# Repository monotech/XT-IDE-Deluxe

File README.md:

Monotech XT-IDE Deluxe v1.2 ReadMe
----

Bootable 8-bit ISA CF+IDE interface

Documentation for the switches can be found on the rear silkscreen.

If you wish to build one yourself, generate a gerber, and use the provided Bill Of Materials.
It uses a Keystone 9202 bracket, with a slot and hole cut for the CF slot and activity LED respectively.

I may have stock of these for sale at monotech.fwscart.com

Credit:
----
Design uses some of the schematic from XT-IDE Rev2 and Glitchworks
www.vcfed.org/forum/showthread.php?29202-XTIDE-Rev2
github.com/glitchwrks/xt_ide

The board is designed to carry XT-IDE Universal BIOS on the ROM
www.xtideuniversalbios.org

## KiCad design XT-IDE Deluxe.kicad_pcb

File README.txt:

Monotech XT-IDE rev 5.1 ReadMe
----------------------------

8-bit ISA IDE interface + Boot ROM (two separate functions that can be used individually).

Documentation for the switches can be found on the rear silkscreen.

Credit:
-------
Design uses schematic from Glitchworks, with a few small changes to switches
PCB is made from scratch with rough IC layout based on Glitchworks for ease of routing.
https://github.com/glitchwrks/xt_ide

XT-IDE Universal BIOS
https://code.google.com/archive/p/xtideuniversalbios/

Changelog:

rev 5.1:
Slightly different PCB shape so switches no longer protruded past PCB edge, getting in the way when pushing the card into a tight slot.
Some silkscreen documentation clarifying.
Changed capacitor hole spacing to much more common 5mm.

rev 5:
Initial release

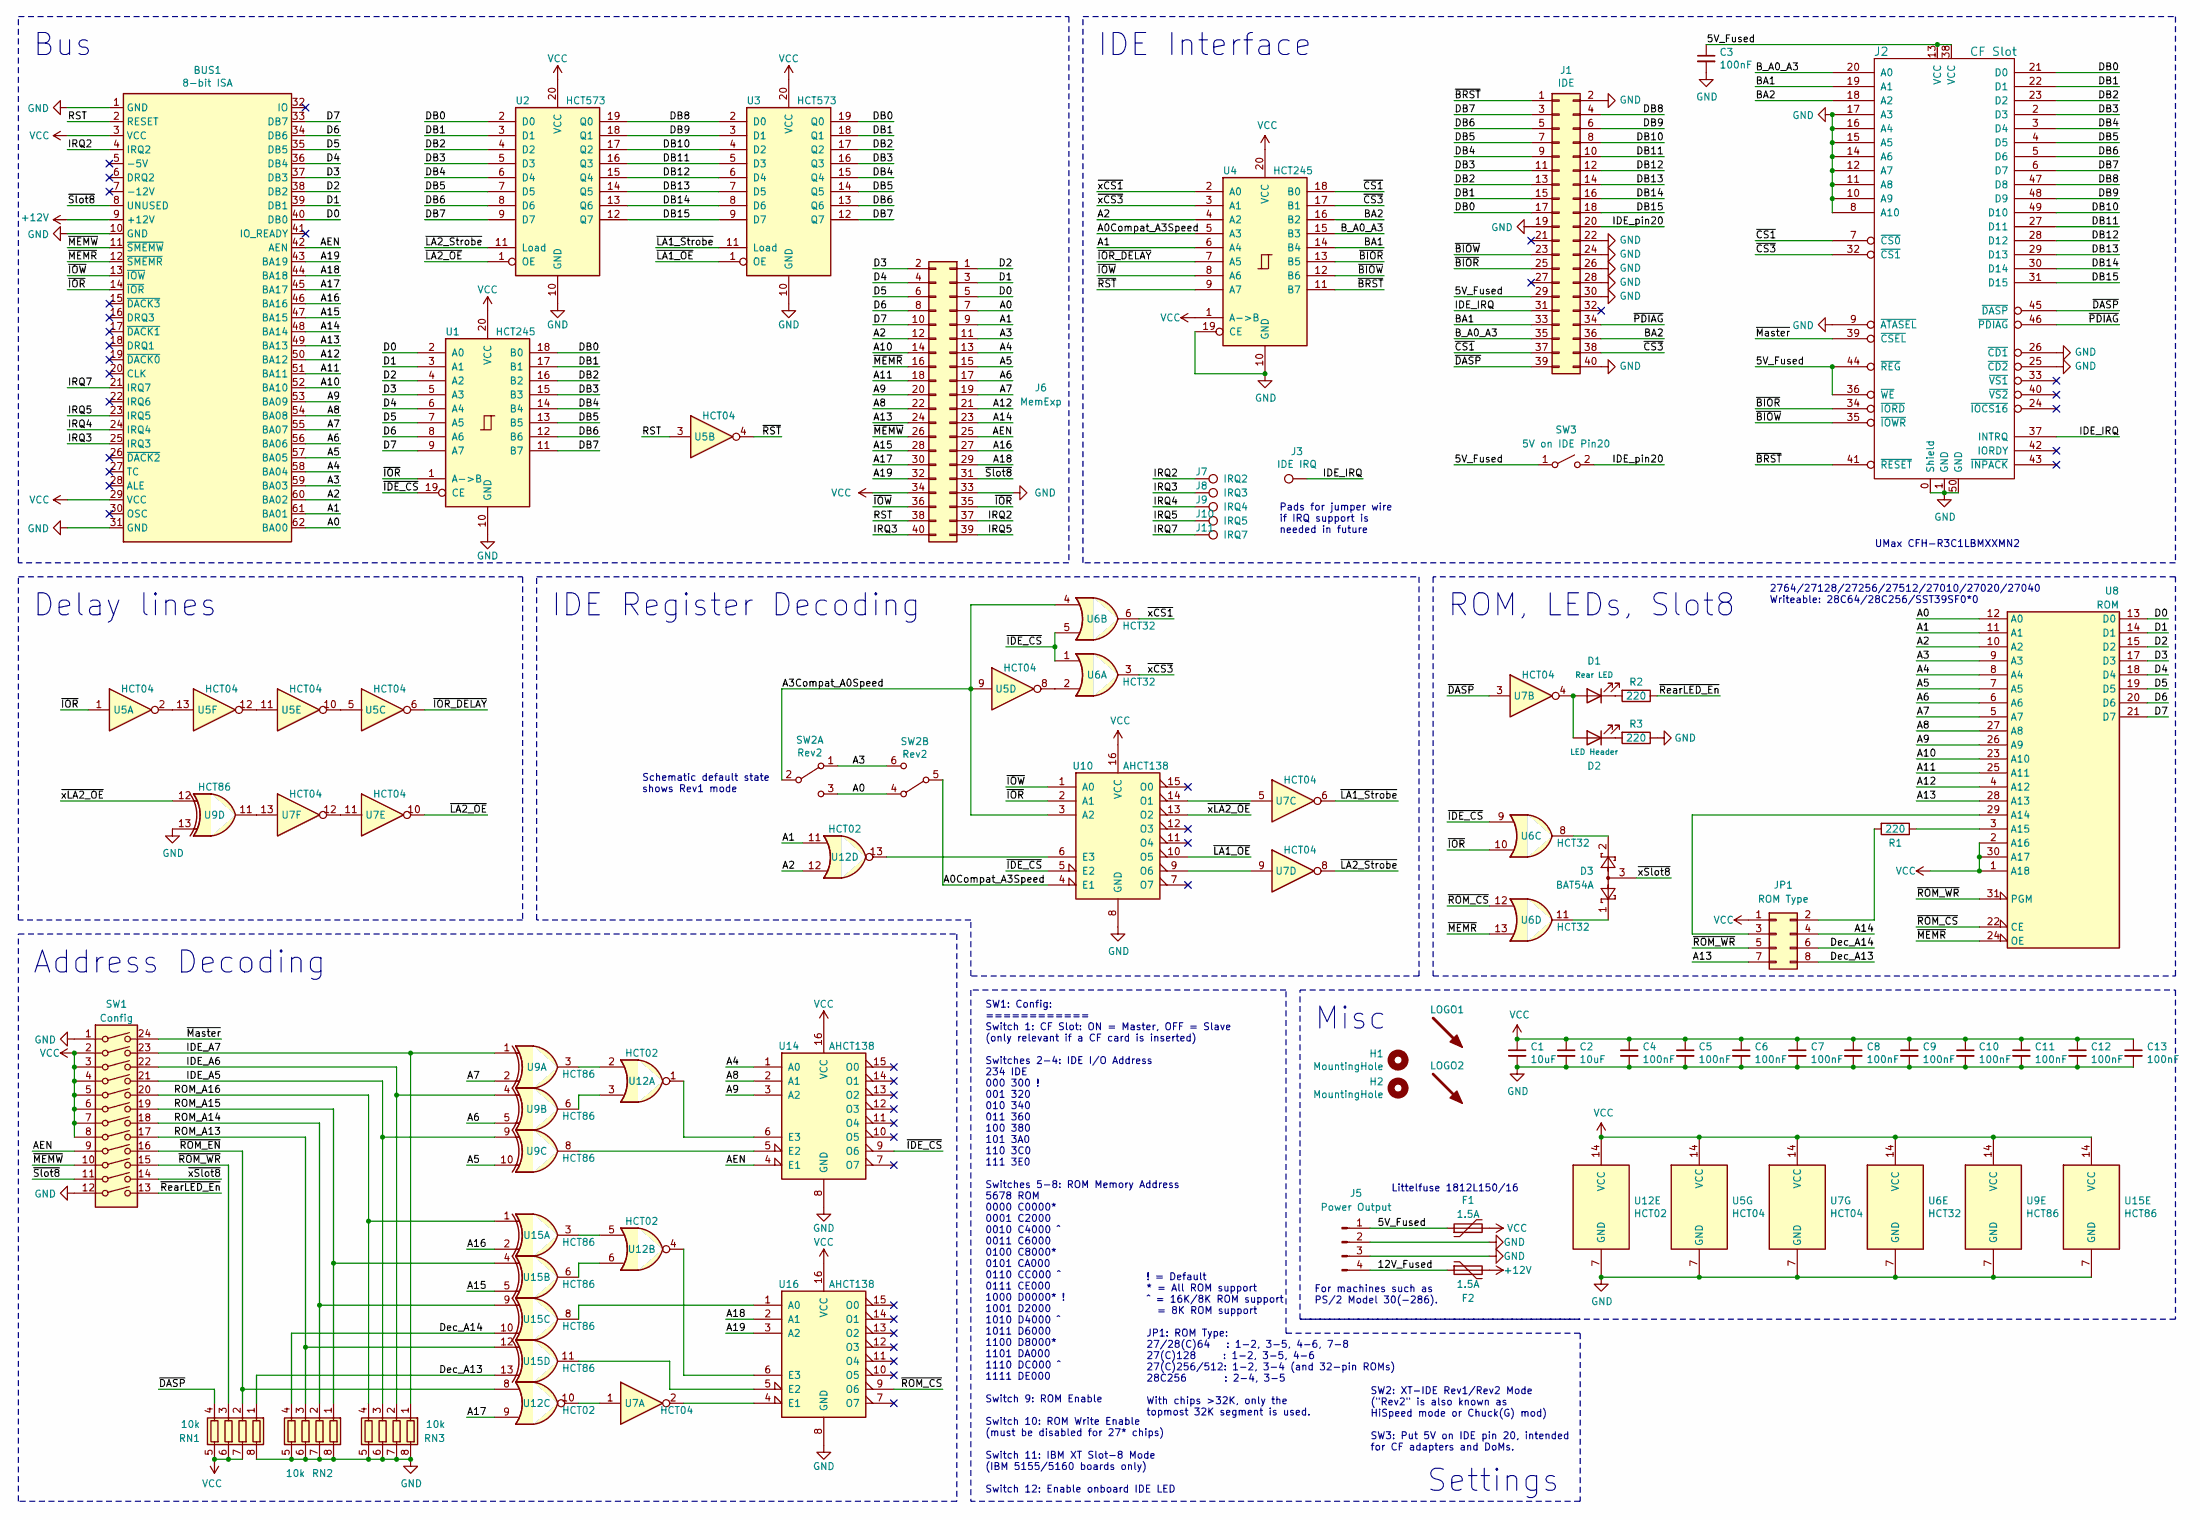
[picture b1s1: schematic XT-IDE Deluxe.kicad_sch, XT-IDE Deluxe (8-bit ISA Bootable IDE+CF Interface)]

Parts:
BUS1: 8-bit ISA; ISA-8BIT-XT-IDE
C1, C2: 10uF; C_0603_1608Metric
C3, C4, C5, C6, C7, C8, C9, C10, C11, C12, C13: 100nF; C_0603_1608Metric
D1: Rear LED; 3mm_LED_RightAngle
D2: LED Header; PinHeader_1x02_P2.54mm_Horizontal
D3: BAT54A; SOT-23
F1, F2: 1.5A; Fuse_1812_4532Metric
H1, H2: MountingHole; MountingHole_3.2mm_M3
J1: IDE; IDC-20_P2.54mm_Vertical_SMD
J2: CF Slot; CF_Slot_UMax_CFH-R3C1LBMXXMN2
J3: IDE IRQ; TestPoint_Pad_1.0x1.0mm
J5: Power Output; PinHeader_1x04_P2.54mm_Horizontal
J6: MemExp; MicroRAM_Expansion
J7: IRQ2; TestPoint_Pad_1.0x1.0mm
J8: IRQ3; TestPoint_Pad_1.0x1.0mm
J9: IRQ4; TestPoint_Pad_1.0x1.0mm
J10: IRQ5; TestPoint_Pad_1.0x1.0mm
J11: IRQ7; TestPoint_Pad_1.0x1.0mm
JP1: ROM Type; PinHeader_2x04_P2.54mm_Vertical_SMD
LOGO1: SYM_Arrow45_Large; Monotech Logo 12mm
LOGO2: SYM_Arrow45_Large; XT-IDE Deluxe
R1, R2, R3: 220; R_0805_2012Metric
RN1, RN2, RN3: 10k; R_Array_Convex_4x0603
SW1: Config; SW_DIP_SPSTx12_Slide_6.7x32.04mm_W8.61mm_P2.54mm_LowProfile
SW2: Rev2; SW_DPDT_MS-22D28-G020
SW3: 5V on IDE Pin20; SW_DPDT_MS-22D28-G020
U1, U4: HCT245; TSSOP-20_4.4x6.5mm_P0.65mm
U2, U3: HCT573; TSSOP-20_4.4x6.5mm_P0.65mm
U5, U7: HCT04; SOIC-14_3.9x8.7mm_P1.27mm
U6: HCT32; SOIC-14_3.9x8.7mm_P1.27mm
U8: ROM; DIP-32_W16.51mm_SMDSocket_LongPads
U9, U15: HCT86; SOIC-14_3.9x8.7mm_P1.27mm
U10, U14, U16: AHCT138; SOIC-16_3.9x9.9mm_P1.27mm
U12: HCT02; SOIC-14_3.9x8.7mm_P1.27mm

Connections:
+12V: BUS1.9 (+12V), F2.2
/5V_Fused: C3.1, F1.1, J1.29, J2.13 (VCC), J2.36 (~WE), J2.38 (VCC), J2.44 (~REG), J5.1, SW3.1 (A)
/12V_Fused: F2.1, J5.4
/A0: BUS1.62 (BA00), J6.7, SW2.3 (C), SW2.4 (A), U8.12 (A0)
/A0Compat_A3Speed: SW2.5 (B), U4.5 (A3), U10.4 (E1)
/A1: BUS1.61 (BA01), J6.9, U4.6 (A4), U8.11 (A1), U12.11
/A2: BUS1.60 (BA02), J6.12, U4.4 (A2), U8.10 (A2), U12.12
/A3: BUS1.59 (BA03), J6.11, SW2.1 (A), SW2.6 (C), U8.9 (A3)
/A3Compat_A0Speed: SW2.2 (B), U5.9, U6.4, U10.3 (A2)
/A4: BUS1.58 (BA04), J6.13, U8.8 (A4), U14.1 (A0)
/A5: BUS1.57 (BA05), J6.15, U8.7 (A5), U9.10
/A6: BUS1.56 (BA06), J6.17, U8.6 (A6), U9.5
/A7: BUS1.55 (BA07), J6.19, U8.5 (A7), U9.2
/A8: BUS1.54 (BA08), J6.22, U8.27 (A8), U14.2 (A1)
/A9: BUS1.53 (BA09), J6.20, U8.26 (A9), U14.3 (A2)
/A10: BUS1.52 (BA10), J6.14, U8.23 (A10)
/A11: BUS1.51 (BA11), J6.18, U8.25 (A11)
/A12: BUS1.50 (BA12), J6.21, U8.4 (A12)
/A13: BUS1.49 (BA13), J6.24, JP1.7, U8.28 (A13)
/A14: BUS1.48 (BA14), J6.23, JP1.4
/A15: BUS1.47 (BA15), J6.28, U15.5
/A16: BUS1.46 (BA16), J6.27, U15.2
/A17: BUS1.45 (BA17), J6.30, U12.9
/A18: BUS1.44 (BA18), J6.29, U16.2 (A1)
/A19: BUS1.43 (BA19), J6.32, U16.3 (A2)
/AEN: BUS1.42 (AEN), J6.25, SW1.9, U14.4 (E1)
/BA1: J1.33, J2.19 (A1), U4.14 (B4)
/BA2: J1.36, J2.18 (A2), U4.16 (B2)
/B_A0_A3: J1.35, J2.20 (A0), U4.15 (B3)
/D0: BUS1.40 (DB0), J6.5, U1.2 (A0), U8.13 (D0)
/D1: BUS1.39 (DB1), J6.3, U1.3 (A1), U8.14 (D1)
/D2: BUS1.38 (DB2), J6.1, U1.4 (A2), U8.15 (D2)
/D3: BUS1.37 (DB3), J6.2, U1.5 (A3), U8.17 (D3)
/D4: BUS1.36 (DB4), J6.4, U1.6 (A4), U8.18 (D4)
/D5: BUS1.35 (DB5), J6.6, U1.7 (A5), U8.19 (D5)
/D6: BUS1.34 (DB6), J6.8, U1.8 (A6), U8.20 (D6)
/D7: BUS1.33 (DB7), J6.10, U1.9 (A7), U8.21 (D7)
/DB0: J1.17, J2.21 (D0), U1.18 (B0), U2.2 (D0), U3.19 (Q0)
/DB1: J1.15, J2.22 (D1), U1.17 (B1), U2.3 (D1), U3.18 (Q1)
/DB2: J1.13, J2.23 (D2), U1.16 (B2), U2.4 (D2), U3.17 (Q2)
/DB3: J1.11, J2.2 (D3), U1.15 (B3), U2.5 (D3), U3.16 (Q3)
/DB4: J1.9, J2.3 (D4), U1.14 (B4), U2.6 (D4), U3.15 (Q4)
/DB5: J1.7, J2.4 (D5), U1.13 (B5), U2.7 (D5), U3.14 (Q5)
/DB6: J1.5, J2.5 (D6), U1.12 (B6), U2.8 (D6), U3.13 (Q6)
/DB7: J1.3, J2.6 (D7), U1.11 (B7), U2.9 (D7), U3.12 (Q7)
/DB8: J1.4, J2.47 (D8), U2.19 (Q0), U3.2 (D0)
/DB9: J1.6, J2.48 (D9), U2.18 (Q1), U3.3 (D1)
/DB10: J1.8, J2.49 (D10), U2.17 (Q2), U3.4 (D2)
/DB11: J1.10, J2.27 (D11), U2.16 (Q3), U3.5 (D3)
/DB12: J1.12, J2.28 (D12), U2.15 (Q4), U3.6 (D4)
/DB13: J1.14, J2.29 (D13), U2.14 (Q5), U3.7 (D5)
/DB14: J1.16, J2.30 (D14), U2.13 (Q6), U3.8 (D6)
/DB15: J1.18, J2.31 (D15), U2.12 (Q7), U3.9 (D7)
/Dec_A13: JP1.8, RN1.1 (R1.1), U15.13
/Dec_A14: JP1.6, RN2.4 (R4.1), U15.10
/IDE_A5: RN3.3 (R3.1), SW1.21, U9.9
/IDE_A6: RN3.2 (R2.1), SW1.22, U9.4
/IDE_A7: RN3.1 (R1.1), SW1.23, U9.1
/IDE_IRQ: J1.31, J2.37 (INTRQ), J3.1
/IDE_pin20: J1.20, SW3.2 (B)
/IRQ2: BUS1.4 (IRQ2), J6.37, J7.1
/IRQ3: BUS1.25 (IRQ3), J6.40, J8.1
/IRQ4: BUS1.24 (IRQ4), J9.1
/IRQ5: BUS1.23 (IRQ5), J6.39, J10.1
/IRQ7: BUS1.21 (IRQ7), J11.1
/ROM_A13: RN2.3 (R3.1), SW1.17, U15.12
/ROM_A14: RN2.2 (R2.1), SW1.18, U15.9
/ROM_A15: RN2.1 (R1.1), SW1.19, U15.4
/ROM_A16: RN3.4 (R4.1), SW1.20, U15.1
/RST: BUS1.2 (RESET), J6.38, U5.3
/~BIOR: J1.25, J2.34 (~IORD), U4.13 (B5)
/~BIOW: J1.23, J2.35 (~IOWR), U4.12 (B6)
/~BRST: J1.1, J2.41 (~RESET), U4.11 (B7)
/~CS1: J1.37, J2.7 (~CS0), U4.18 (B0)
/~CS3: J1.38, J2.32 (~CS1), U4.17 (B1)
/~DASP: J1.39, J2.45 (~DASP), RN1.4 (R4.1), U7.3
/~IDE_CS: U1.19 (CE), U6.1, U6.5, U6.9, U10.5 (E2), U14.9 (O6)
/~IOR_DELAY: U4.7 (A5), U5.6
/~IOR: BUS1.14 (~IOR), J6.35, U1.1 (A->B), U5.1, U6.10, U10.2 (A1)
/~IOW: BUS1.13 (~IOW), J6.36, U4.8 (A6), U10.1 (A0)
/~LA1_OE: U3.1 (OE), U10.10 (O5)
/~LA1_Strobe: U3.11 (Load), U7.6
/~LA2_OE: U2.1 (OE), U7.10
/~LA2_Strobe: U2.11 (Load), U7.8
/~MEMR: BUS1.12 (~SMEMR), J6.16, U6.13, U8.24 (OE)
/~MEMW: BUS1.11 (~SMEMW), J6.26, SW1.10
/~Master: J2.39 (~CSEL), SW1.24
/~PDIAG: J1.34, J2.46 (~PDIAG)
/~ROM_CS: U6.12, U8.22 (CE), U16.9 (O6)
/~ROM_EN: RN1.2 (R2.1), SW1.16, U12.8
/~ROM_WR: JP1.5, RN1.3 (R3.1), SW1.15, U8.31 (PGM)
/~RST: U4.9 (A7), U5.4
/~RearLED_En: R2.1, SW1.13
/~Slot8: BUS1.8 (UNUSED), J6.31, SW1.11
/~xCS1: U4.2 (A0), U6.6
/~xCS3: U4.3 (A1), U6.3
/~xLA2_OE: U9.12, U10.13 (O2)
/~xSlot8: D3.3, SW1.14
GND: BUS1.1 (GND), BUS1.10 (GND), BUS1.31 (GND), C1.2, C2.2, C3.2, C4.2, C5.2, C6.2, C7.2, C8.2, C9.2, C10.2, C11.2, C12.2, C13.2, J1.2, J1.19, J1.22, J1.24, J1.26, J1.28, J1.30, J1.40, J2.0 (Shield), J2.1 (GND), J2.8 (A10), J2.9 (~ATASEL), J2.10 (A9), J2.11 (A8), J2.12 (A7), J2.14 (A6), J2.15 (A5), J2.16 (A4), J2.17 (A3), J2.25 (~CD2), J2.26 (~CD1), J2.50 (GND), J5.2, J5.3, J6.33, R3.1, RN1.8 (R1.2), RN2.5 (R4.2), RN2.6 (R3.2), RN2.7 (R2.2), RN2.8 (R1.2), RN3.5 (R4.2), RN3.6 (R3.2), RN3.7 (R2.2), RN3.8 (R1.2), SW1.1, SW1.12, U1.10 (GND), U2.10 (GND), U3.10 (GND), U4.10 (GND), U4.19 (CE), U5.7 (GND), U6.7 (GND), U7.7 (GND), U8.16 (GND), U9.7 (GND), U9.13, U10.8 (GND), U12.7 (GND), U14.8 (GND), U15.7 (GND), U16.8 (GND)
unnamed: D1.1 (K), R2.2
unnamed: D1.2 (A), D2.2 (A), U7.4
unnamed: D2.1 (K), R3.2
unnamed: D3.1, U6.11
unnamed: D3.2, U6.8
unnamed: JP1.2, R1.2
unnamed: JP1.3, U8.29 (A14)
unnamed: R1.1, U8.3 (A15)
unnamed: U5.8, U6.2
unnamed: U5.5, U5.10
unnamed: U5.11, U5.12
unnamed: U5.2, U5.13
unnamed: U7.11, U7.12
unnamed: U7.13, U9.11
unnamed: U10.6 (E3), U12.13
unnamed: U7.9, U10.9 (O6)
unnamed: U7.5, U10.14 (O1)
unnamed: U12.1, U14.6 (E3)
unnamed: U9.3, U12.2
unnamed: U9.6, U12.3
unnamed: U12.4, U16.6 (E3)
unnamed: U12.5, U15.3
unnamed: U12.6, U15.6
unnamed: U7.1, U12.10
unnamed: U9.8, U14.5 (E2)
unnamed: U15.8, U16.1 (A0)
unnamed: U15.11, U16.5 (E2)
unnamed: U7.2, U16.4 (E1)
VCC: BUS1.3 (VCC), BUS1.29 (VCC), C1.1, C2.1, C4.1, C5.1, C6.1, C7.1, C8.1, C9.1, C10.1, C11.1, C12.1, C13.1, F1.2, J6.34, JP1.1, RN1.5 (R4.2), RN1.6 (R3.2), RN1.7 (R2.2), SW1.2, SW1.3, SW1.4, SW1.5, SW1.6, SW1.7, SW1.8, U1.20 (VCC), U2.20 (VCC), U3.20 (VCC), U4.1 (A->B), U4.20 (VCC), U5.14 (VCC), U6.14 (VCC), U7.14 (VCC), U8.1 (A18), U8.2 (A16), U8.30 (A17), U8.32 (VCC), U9.14 (VCC), U10.16 (VCC), U12.14 (VCC), U14.16 (VCC), U15.14 (VCC), U16.16 (VCC)

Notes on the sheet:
Bus
Littelfuse 1812L150/16
For machines such as PS/2 Model 30(-286).
! = Default * = All ROM support ^ = 16K/8K ROM support = 8K ROM support JP1: ROM Type: 27/28(C)64 : 1-2, 3-5, 4-6, 7-8 27(C)128 : 1-2, 3-5, 4-6 27(C)256/512: 1-2, 3-4 (and 32-pin ROMs) 28C256 : 2-4, 3-5 With chips >32K, only the topmost 32K segment is used.
Misc
IDE Register Decoding
Pads for jumper wire if IRQ support is needed in future
SW2: XT-IDE Rev1/Rev2 Mode ("Rev2" is also known as HiSpeed mode or Chuck(G) mod) SW3: Put 5V on IDE pin 20, intended for CF adapters and DoMs.
Delay lines
IDE Interface
SW1: Config: ============ Switch 1: CF Slot: ON = Master, OFF = Slave (only relevant if a CF card is inserted) Switches 2-4: IDE I/O Address 234 IDE 000 300 ! 001 320 010 340 011 360 100 380 101 3A0 110 3C0 111 3E0 Switches 5-8: ROM Memory Address 5678 ROM 0000 C0000* 0001 C2000 0010 C4000 ^ 0011 C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
Schematic default state shows Rev1 mode
UMax CFH-R3C1LBMXXMN2
2764/27128/27256/27512/27010/27020/27040 Writeable: 28C64/28C256/SST39SF0*0
ROM, LEDs, Slot8
Address Decoding
Settings

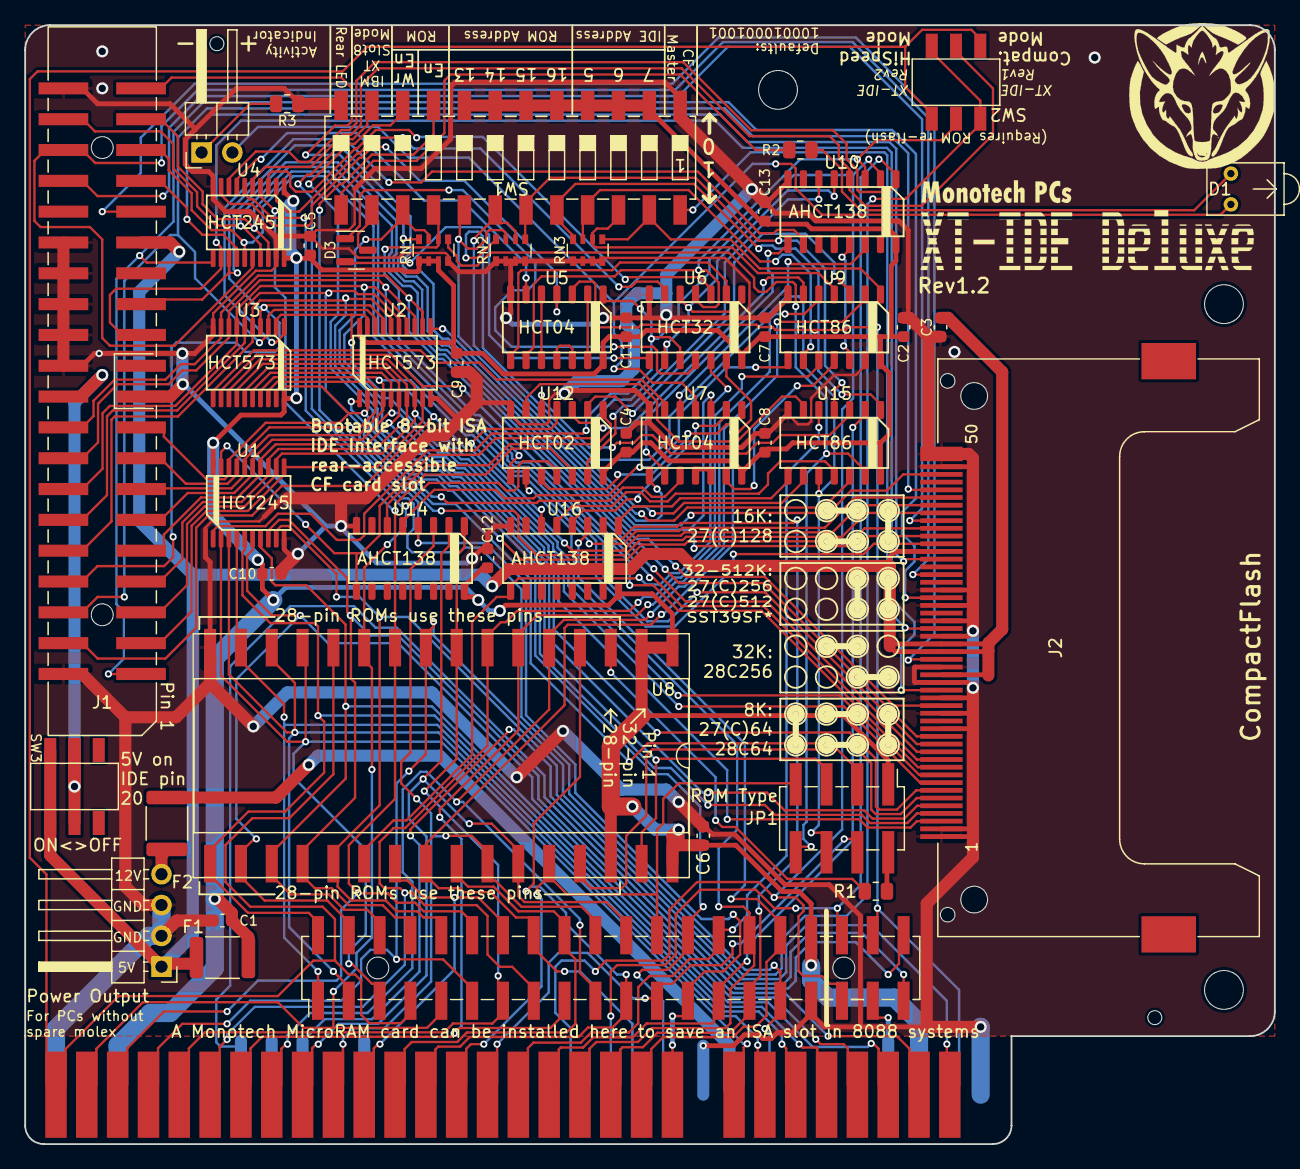
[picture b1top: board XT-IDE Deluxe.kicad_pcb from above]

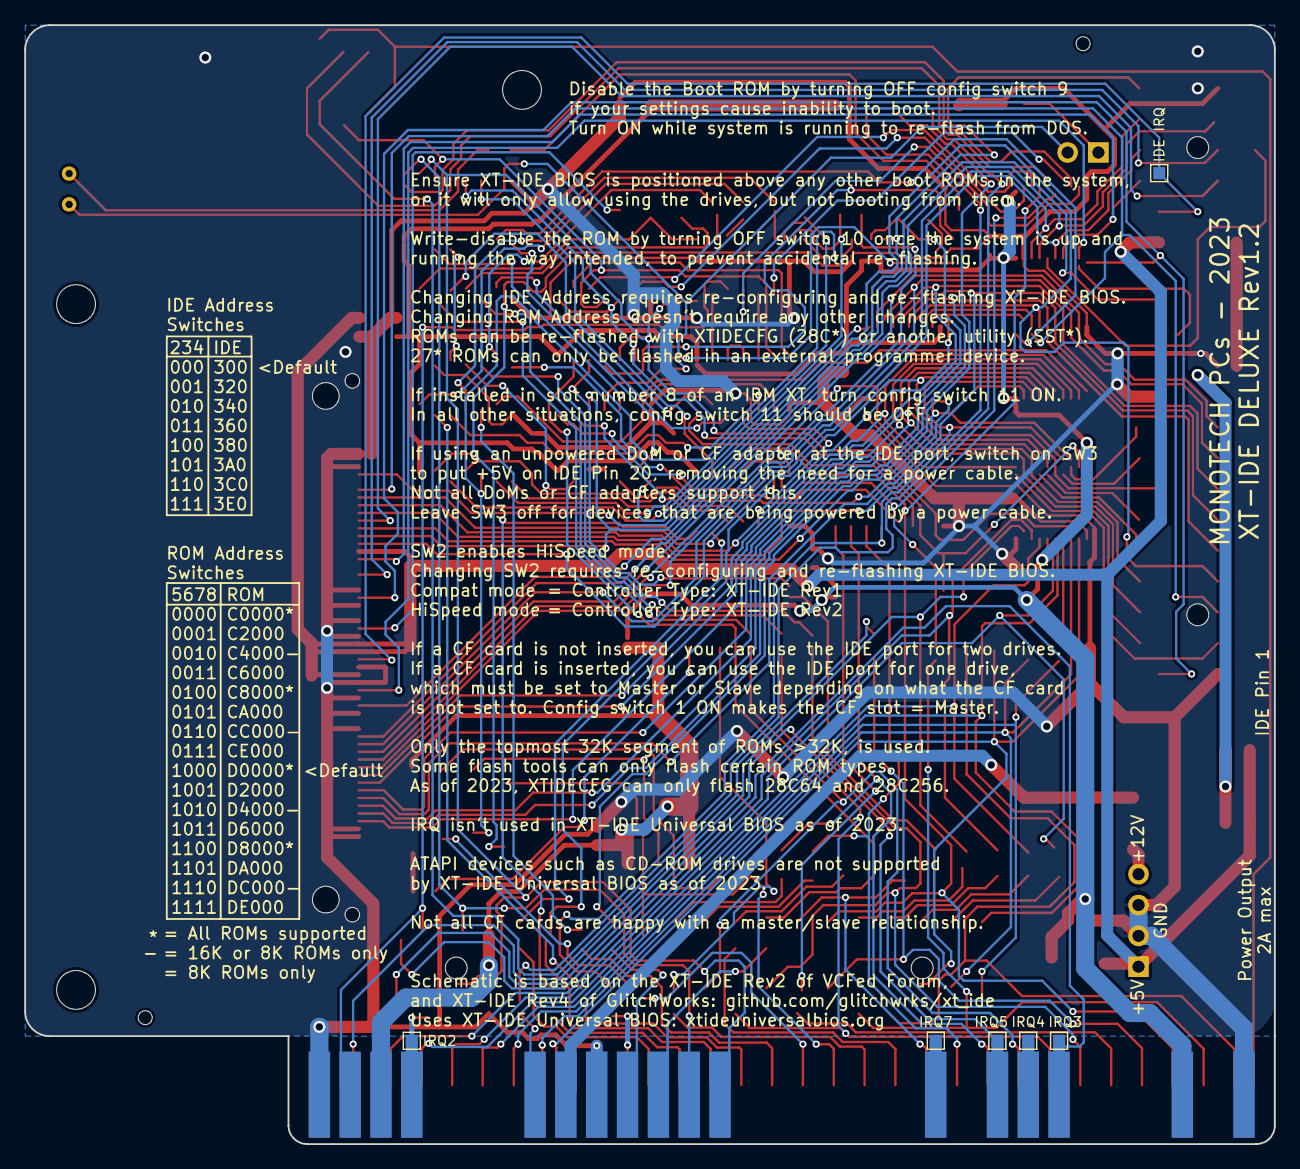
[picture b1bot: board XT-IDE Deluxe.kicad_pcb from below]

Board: 2 copper layers, 103.0 x 92.2 mm, 57 parts (6 on the bottom side), 128 nets.

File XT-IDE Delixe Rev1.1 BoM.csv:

Ref,Qnty,Value,Footprint,Mouser Part
"C1, C2, ",2,10uF,0805,187-CL21A106KOQNNNG 
"C3, C4, C5, C6, C7, C8, C9, C10, C11, C12, ",10,100nF,0805,603-CC805KRX7R9BB104 
"D1, ",1,LED,0805,710-150080SS75000 
"D2, ",1,LED,2.54mm,649-1012937990202BLF 
"F1, F2, ",2,1.5A,1206,530-C1T1.5 
"J1, ",1,IDE,IDC-40,710-61204021621 
"J2, ",1,CF_Adapter,2x20_2.54mm,710-61304021821 
"J5, ",1,Power Output,,571-1718264 
"J6, ",1,MemExp,2x17_2.54mm,649-67996-434HLF 
"JP1, ",1,5V on IDE Pin20,2.54mm,649-54102-T0800LF 
"R1, R2, ",2,1k,0805,652-CRT0805FZ1001ELF 
"RN1, RN2, RN3, ",3,10k,4x0603,791-WA06X103JTL 
"SW1, ",1,HiSpeed,,611-JS202011CQN 
"SW2, ",1,Config,DIP-24,774-20812 
"U1, U4, ",2,HCT245,TSSOP-20,595-SN74HCT245PW 
"U2, U3, ",2,HCT573,SOIC-20,863-MC74HCT573ADWG 
"U5, U7, ",2,HCT04,SOIC-14,595-SN74HCT04DRG4 
"U6, ",1,HCT32,SOIC-14,595-SN74HCT32D 
"U8, ",1,DIP_Socket,DIP-28,571-1-2199299-2 
"U9, U15, ",2,HCT86,SOIC-14,595-CD74HCT86M 
"U10, U14, U16, ",3,F138,SOIC-16,595-SN74F138D 
"U12, ",1,HCT02,SOIC-14,595-SN74HCT02DR 
"U13, ",1,AHC1G09,SC-70-5,595-SN74AHC1G09DCKR

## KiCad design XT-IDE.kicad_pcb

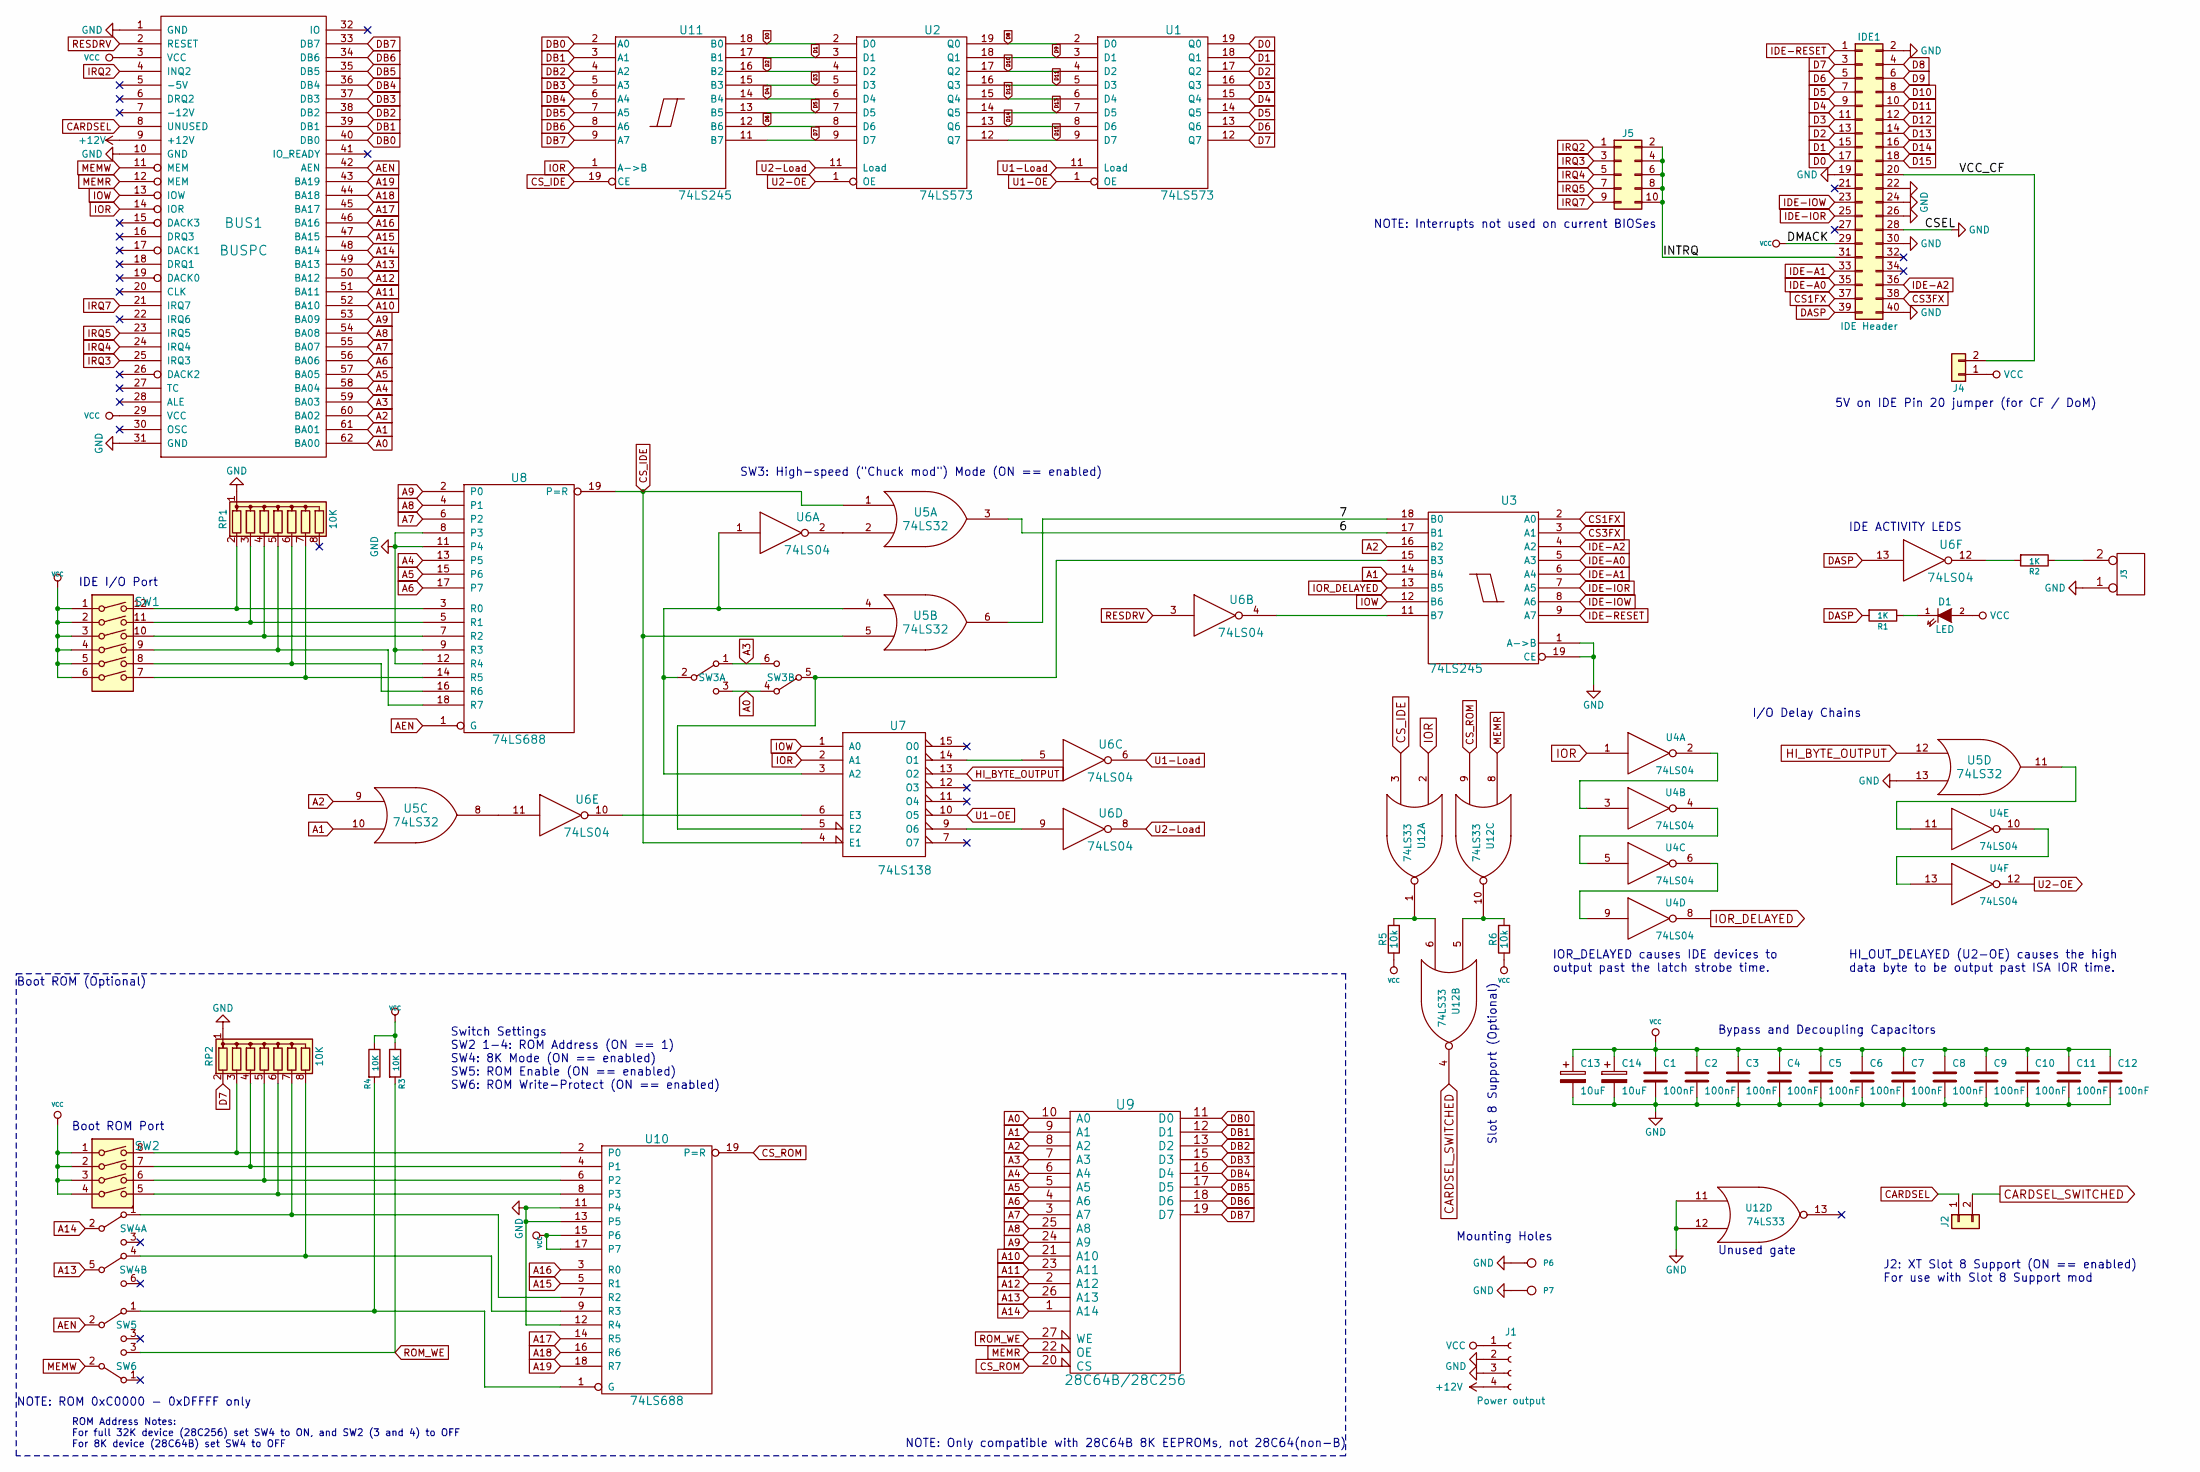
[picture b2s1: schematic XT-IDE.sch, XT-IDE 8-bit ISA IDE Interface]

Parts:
BUS1: BUSPC; ISA-8BIT-XT-IDE
C1, C2, C3, C4, C5, C6, C7, C8, C9, C10, C11: 100nF; C_Disc_D4.3mm_W1.9mm_P5.00mm
C12: 100nF; C_0805_2012Metric_Pad1.15x1.40mm_HandSolder
C13, C14: 10uF; CP_Radial_Tantal_D4.5mm_P5.00mm
D1: LED; LED_D5.0mm
IDE1: IDE Header; Pin_Header_Angled_2x20_Pitch2.54mm_Shrouded
J1: Power output; PinHeader_1x04_P2.54mm_Horizontal
J2, J4: Conn_01x02; PinHeader_1x02_P2.54mm_Vertical
J3: External LED; PinHeader_1x02_P2.54mm_Horizontal
J5: Conn_02x05_Odd_Even; PinHeader_2x05_P2.54mm_Vertical
P6, P7: CONN_1; MountingHole_3.2mm_M3
R1, R2: 1K; R_Axial_DIN0207_L6.3mm_D2.5mm_P7.62mm_Horizontal
R3, R4: 10K; R_Axial_DIN0207_L6.3mm_D2.5mm_P7.62mm_Horizontal
R5, R6: 10k; R_0805_2012Metric_Pad1.15x1.40mm_HandSolder
RP1, RP2: 10K; R_Array_SIP9
SW1: IDE Address; SW_DIP_SPSTx06_Slide_9.78x17.42mm_W7.62mm_P2.54mm
SW2: ROM Address; SW_DIP_SPSTx04_Slide_9.78x12.34mm_W7.62mm_P2.54mm
SW3: DPDT; CKCOMP-OS202011MA0QS1
SW4: DPDT; SW_MS-22D18G2
SW5, SW6: SPDT; SW_CuK_OS102011MA1QN1_SPDT_Angled
U1, U2: 74LS573; DIP-20_W7.62mm
U3, U11: 74LS245; DIP-20_W7.62mm
U4, U6: 74LS04; DIP-14_W7.62mm
U5: 74LS32; DIP-14_W7.62mm
U7: 74LS138; DIP-16_W7.62mm
U8, U10: 74LS688; DIP-20_W7.62mm
U9: 28C64B/28C256; DIP-28_W15.24mm_Socket
U12: 74LS33; SOIC-14_3.9x8.7mm_P1.27mm

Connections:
+12V: BUS1.9 (+12V), J1.4
/6: U3.17 (B1), U5.3
/7: U3.18 (B0), U5.6
/INTRQ: IDE1.31, J5.2, J5.4, J5.6, J5.8, J5.10
/VCC_CF: IDE1.20, J4.2
A0: BUS1.62 (BA00), SW3.3 (C), SW3.4 (A), U9.10 (A0)
A1: BUS1.61 (BA01), U3.14 (B4), U5.10, U9.9 (A1)
A2: BUS1.60 (BA02), U3.16 (B2), U5.9, U9.8 (A2)
A3: BUS1.59 (BA03), SW3.1 (A), SW3.6 (C), U9.7 (A3)
A4: BUS1.58 (BA04), U8.13 (P5), U9.6 (A4)
A5: BUS1.57 (BA05), U8.15 (P6), U9.5 (A5)
A6: BUS1.56 (BA06), U8.17 (P7), U9.4 (A6)
A7: BUS1.55 (BA07), U8.6 (P2), U9.3 (A7)
A8: BUS1.54 (BA08), U8.4 (P1), U9.25 (A8)
A9: BUS1.53 (BA09), U8.2 (P0), U9.24 (A9)
A10: BUS1.52 (BA10), U9.21 (A10)
A11: BUS1.51 (BA11), U9.23 (A11)
A12: BUS1.50 (BA12), U9.2 (A12)
A13: BUS1.49 (BA13), SW4.5 (B), U9.26 (A13)
A14: BUS1.48 (BA14), SW4.2 (B), U9.1 (A14)
A15: BUS1.47 (BA15), U10.5 (R1)
A16: BUS1.46 (BA16), U10.3 (R0)
A17: BUS1.45 (BA17), U10.14 (R5)
A18: BUS1.44 (BA18), U10.16 (R6)
A19: BUS1.43 (BA19), U10.18 (R7)
AEN: BUS1.42 (AEN), SW5.2 (B), U8.1 (G)
CARDSEL: BUS1.8 (UNUSED), J2.1
CARDSEL_SWITCHED: J2.2, U12.4
CS1FX: IDE1.37, U3.2 (A0)
CS3FX: IDE1.38, U3.3 (A1)
CS_IDE: U5.1, U5.5, U7.4 (E1), U8.19 (P=R), U11.19 (CE), U12.3
CS_ROM: U9.20 (CS), U10.19 (P=R), U12.9
D0: IDE1.17, U1.19 (Q0), U2.2 (D0), U11.18 (B0)
D1: IDE1.15, U1.18 (Q1), U2.3 (D1), U11.17 (B1)
D2: IDE1.13, U1.17 (Q2), U2.4 (D2), U11.16 (B2)
D3: IDE1.11, U1.16 (Q3), U2.5 (D3), U11.15 (B3)
D4: IDE1.9, U1.15 (Q4), U2.6 (D4), U11.14 (B4)
D5: IDE1.7, U1.14 (Q5), U2.7 (D5), U11.13 (B5)
D6: IDE1.5, U1.13 (Q6), U2.8 (D6), U11.12 (B6)
D7: IDE1.3, RP2.2 (R1), U1.12 (Q7), U2.9 (D7), U11.11 (B7)
D8: IDE1.4, U1.2 (D0), U2.19 (Q0)
D9: IDE1.6, U1.3 (D1), U2.18 (Q1)
D10: IDE1.8, U1.4 (D2), U2.17 (Q2)
D11: IDE1.10, U1.5 (D3), U2.16 (Q3)
D12: IDE1.12, U1.6 (D4), U2.15 (Q4)
D13: IDE1.14, U1.7 (D5), U2.14 (Q5)
D14: IDE1.16, U1.8 (D6), U2.13 (Q6)
D15: IDE1.18, U1.9 (D7), U2.12 (Q7)
DASP: IDE1.39, R1.2, U6.13
DB0: BUS1.40 (DB0), U9.11 (D0), U11.2 (A0)
DB1: BUS1.39 (DB1), U9.12 (D1), U11.3 (A1)
DB2: BUS1.38 (DB2), U9.13 (D2), U11.4 (A2)
DB3: BUS1.37 (DB3), U9.15 (D3), U11.5 (A3)
DB4: BUS1.36 (DB4), U9.16 (D4), U11.6 (A4)
DB5: BUS1.35 (DB5), U9.17 (D5), U11.7 (A5)
DB6: BUS1.34 (DB6), U9.18 (D6), U11.8 (A6)
DB7: BUS1.33 (DB7), U9.19 (D7), U11.9 (A7)
GND: BUS1.1 (GND), BUS1.10 (GND), BUS1.31 (GND), C1.2, C2.2, C3.2, C4.2, C5.2, C6.2, C7.2, C8.2, C9.2, C10.2, C11.2, C12.2, C13.2, C14.2, IDE1.2, IDE1.19, IDE1.22, IDE1.24, IDE1.26, IDE1.28, IDE1.30, IDE1.40, J1.2, J1.3, J3.1, P6.1, P7.1, RP1.1 (common), RP2.1 (common), U1.10 (GND), U2.10 (GND), U3.1 (A->B), U3.10 (GND), U3.19 (CE), U4.7 (GND), U5.7 (GND), U5.13, U6.7 (GND), U7.8 (GND), U8.8 (P3), U8.9 (R3), U8.10 (GND), U8.11 (P4), U8.12 (R4), U9.14 (GND), U10.10 (GND), U10.11 (P4), U10.12 (R4), U10.13 (P5), U11.10 (GND), U12.7 (GND), U12.11, U12.12
HI_BYTE_OUTPUT: U5.12, U7.13 (O2)
IDE-A0: IDE1.35, U3.5 (A3)
IDE-A1: IDE1.33, U3.6 (A4)
IDE-A2: IDE1.36, U3.4 (A2)
IDE-IOR: IDE1.25, U3.7 (A5)
IDE-IOW: IDE1.23, U3.8 (A6)
IDE-RESET: IDE1.1, U3.9 (A7)
IOR: BUS1.14 (IOR), U4.1, U7.2 (A1), U11.1 (A->B), U12.2
IOR_DELAYED: U3.13 (B5), U4.8
IOW: BUS1.13 (IOW), U3.12 (B6), U7.1 (A0)
IRQ2: BUS1.4 (INQ2), J5.1
IRQ3: BUS1.25 (IRQ3), J5.3
IRQ4: BUS1.24 (IRQ4), J5.5
IRQ5: BUS1.23 (IRQ5), J5.7
IRQ7: BUS1.21 (IRQ7), J5.9
MEMR: BUS1.12 (MEM), U9.22 (OE), U12.8
MEMW: BUS1.11 (MEM), SW6.2 (B)
unnamed: D1.1 (K), R1.1
unnamed: J3.2 (PM), R2.1
unnamed: R2.2, U6.12
unnamed: R4.2, SW5.1 (A), U10.1 (G)
unnamed: R5.2, U12.1, U12.6
unnamed: R6.2, U12.5, U12.10
unnamed: RP1.2 (R1), SW1.12, U8.3 (R0)
unnamed: RP1.3 (R2), SW1.11, U8.5 (R1)
unnamed: RP1.4 (R3), SW1.10, U8.7 (R2)
unnamed: RP1.5 (R4), SW1.9, U8.18 (R7)
unnamed: RP1.6 (R5), SW1.8, U8.16 (R6)
unnamed: RP1.7 (R6), SW1.7, U8.14 (R5)
unnamed: RP2.3 (R2), SW2.8, U10.2 (P0)
unnamed: RP2.4 (R3), SW2.7, U10.4 (P1)
unnamed: RP2.5 (R4), SW2.6, U10.6 (P2)
unnamed: RP2.6 (R5), SW2.5, U10.8 (P3)
unnamed: RP2.7 (R6), SW4.1 (A), U10.7 (R2)
unnamed: RP2.8 (R7), SW4.4 (A), U10.9 (R3)
unnamed: SW3.2 (B), U5.4, U6.1, U7.3 (A2)
unnamed: SW3.5 (B), U3.15 (B3), U7.5 (E2)
unnamed: U3.11 (B7), U6.4
unnamed: U4.2, U4.3
unnamed: U4.4, U4.5
unnamed: U4.6, U4.9
unnamed: U4.10, U4.13
unnamed: U4.11, U5.11
unnamed: U5.2, U6.2
unnamed: U5.8, U6.11
unnamed: U6.5, U7.14 (O1)
unnamed: U6.9, U7.9 (O6)
unnamed: U6.10, U7.6 (E3)
RESDRV: BUS1.2 (RESET), U6.3
ROM_WE: R3.2, SW6.3 (C), U9.27 (WE)
U1-Load: U1.11 (Load), U6.6
U1-OE: U1.1 (OE), U7.10 (O5)
U2-Load: U2.11 (Load), U6.8
U2-OE: U2.1 (OE), U4.12
VCC: BUS1.3 (VCC), BUS1.29 (VCC), C1.1, C2.1, C3.1, C4.1, C5.1, C6.1, C7.1, C8.1, C9.1, C10.1, C11.1, C12.1, C13.1, C14.1, D1.2 (A), IDE1.29, J1.1, J4.1, R3.1, R4.1, R5.1, R6.1, SW1.1, SW1.2, SW1.3, SW1.4, SW1.5, SW1.6, SW2.1, SW2.2, SW2.3, SW2.4, U1.20 (VCC), U2.20 (VCC), U3.20 (VCC), U4.14 (VCC), U5.14 (VCC), U6.14 (VCC), U7.16 (VCC), U8.20 (VCC), U9.28 (VCC), U10.15 (P6), U10.17 (P7), U10.20 (VCC), U11.20 (VCC), U12.14 (VCC)

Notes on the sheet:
5V on IDE Pin 20 jumper (for CF / DoM)
IDE ACTIVITY LEDS
IDE I/O Port
SW3: High-speed ("Chuck mod") Mode (ON == enabled)
NOTE: Only compatible with 28C64B 8K EEPROMs, not 28C64(non-B)
NOTE: ROM 0xC0000 - 0xDFFFF only
Switch Settings SW2 1-4: ROM Address (ON == 1) SW4: 8K Mode (ON == enabled) SW5: ROM Enable (ON == enabled) SW6: ROM Write-Protect (ON == enabled)
ROM Address Notes: For full 32K device (28C256) set SW4 to ON, and SW2 (3 and 4) to OFF For 8K device (28C64B) set SW4 to OFF
Boot ROM (Optional)
Mounting Holes
Bypass and Decoupling Capacitors
NOTE: Interrupts not used on current BIOSes
J2: XT Slot 8 Support (ON == enabled) For use with Slot 8 Support mod
I/O Delay Chains
IOR_DELAYED causes IDE devices to output past the latch strobe time.
HI_OUT_DELAYED (U2-OE) causes the high data byte to be output past ISA IOR time.
Slot 8 Support (Optional)
Boot ROM Port
Unused gate

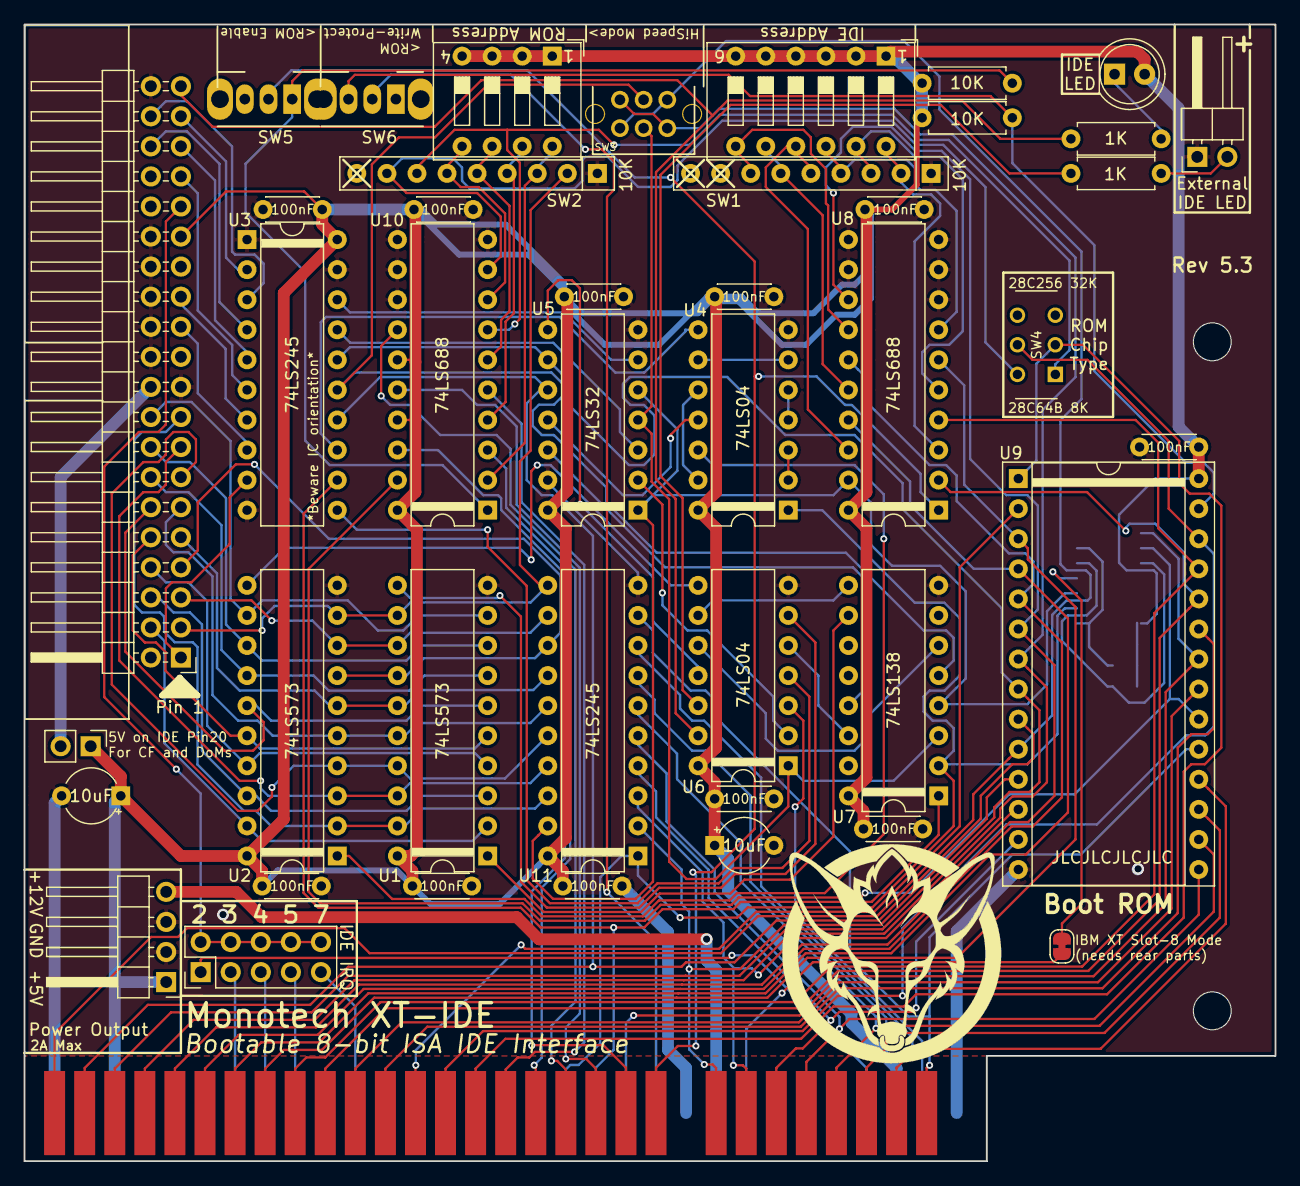
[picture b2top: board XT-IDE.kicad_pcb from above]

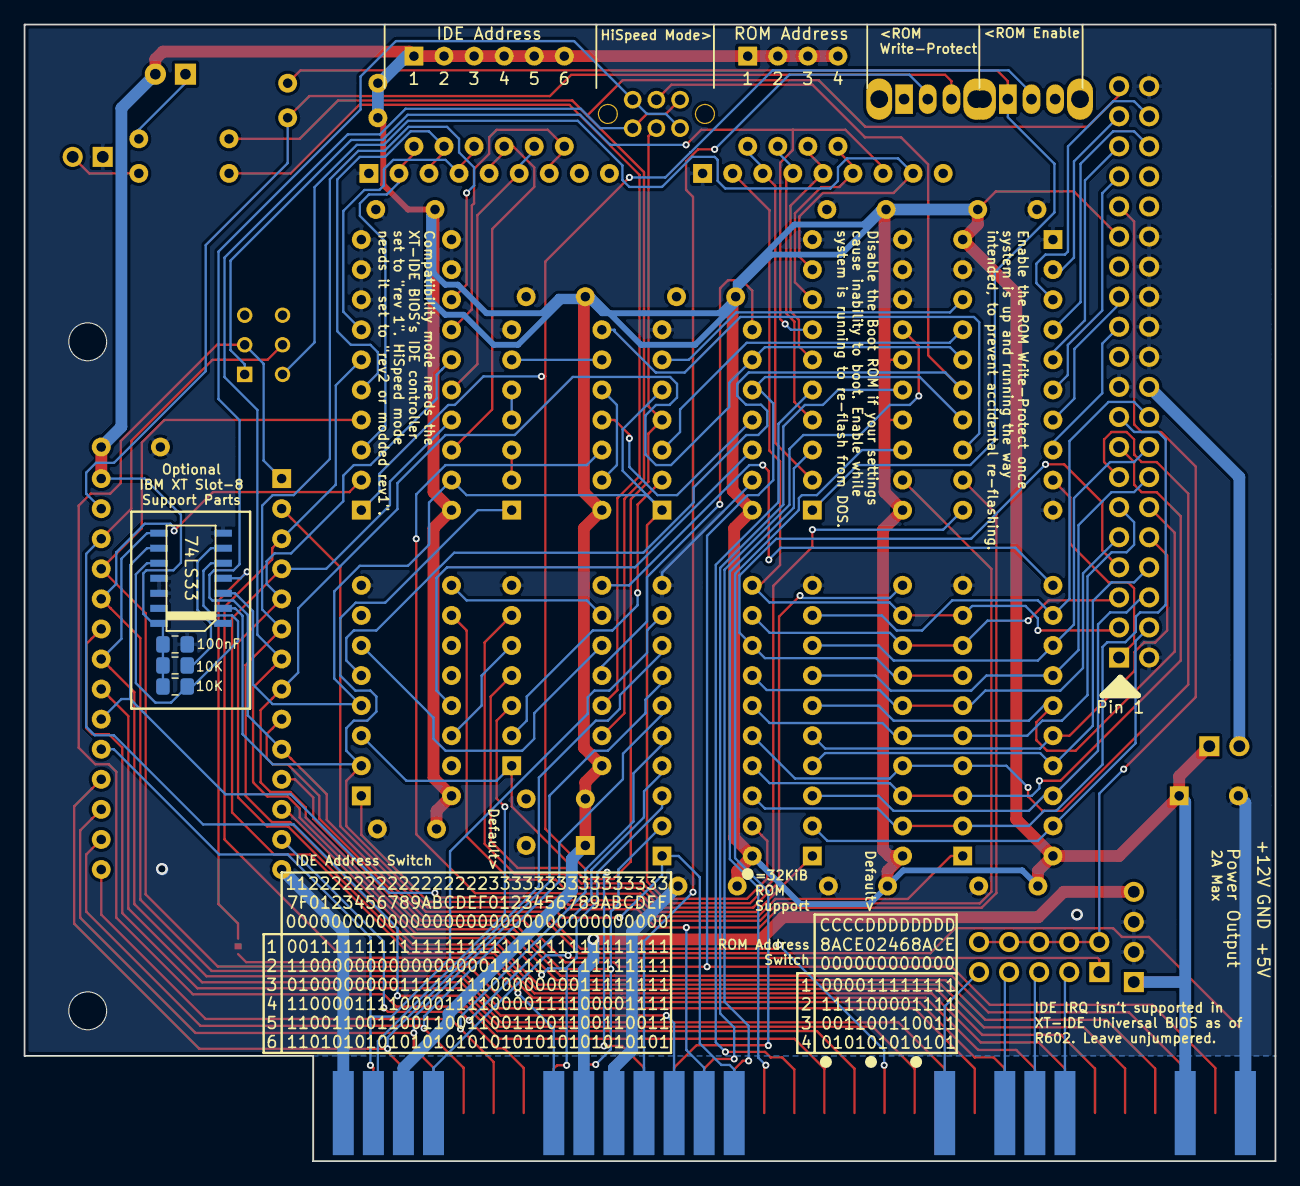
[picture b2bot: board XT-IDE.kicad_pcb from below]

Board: 2 copper layers, 105.7 x 96.0 mm, 50 parts (4 on the bottom side), 113 nets.

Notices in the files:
XT-IDE.kicad_pcb:
GPL v3
